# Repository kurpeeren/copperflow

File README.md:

# copperflow

**A PCB design program you and your AI agent use together.** The agent places, routes, checks and
exports the board through MCP, with or without a window open; you work in the same files in the
editor, and every change it makes is one step you can undo. Schematic, PCB, autorouting, DRC,
Gerbers, BOM and a 3D view, on your own computer.

[Website](https://copperflow.kurpeeren.com) ·
[Download the desktop app](https://github.com/kurpeeren/copperflow/releases/latest) ·
[Connect your agent](https://copperflow.kurpeeren.com/connect.html) ·
`npm install -g copperflow`

<table>
  <tr>
    <td width="50%"></td>
    <td width="50%"></td>
  </tr>
  <tr>
    <td>One agent session, an empty folder, no window open: 23 of 23 connections routed, 0 errors, 16 files for the factory.</td>
    <td>The board as made, drawn from the same Gerber layers the factory gets.</td>
  </tr>
</table>

Circuits are TSX files with elements such as `<board>`, `<resistor>` and `<trace>`, which
copperflow builds and draws with its own engine. You and your agent work on them together:

- the agent changes the circuit through an MCP server, and every change is one undo step;
- you lock the parts you have placed, and the agent cannot move or change them;
- you leave marks such as "route ground here", and the agent reads them;
- edits are written back as minimal text changes, so the rest of your code stays as you wrote it.

Everything runs locally. There is no chat inside copperflow: use the agent you already use,
for example Claude Code or Claude Desktop, through MCP.

> **Status: 0.5, early.** The core, the MCP server, the CLI, the editor, the desktop app, the parts
> library, placement, routing and the fabrication export work. Expect rough edges; see
> [docs/design.md](docs/design.md).

## Quick start

Requires Node.js 22 or newer.

```bash
npm install -g copperflow
```

To work on copperflow itself, install it from source instead:

```bash
git clone https://github.com/kurpeeren/copperflow.git
cd copperflow
npm install
npm run build
npm link
```

Try it on the example board (in the source tree):

```bash
copperflow summary --root examples/usb-c-ldo index.circuit.tsx
```

`copperflow check` (and the agent's `check_circuit`) runs copperflow's own rule checks and nothing else, so no other tool needs to be installed:

- the electrical rules check (ERC): pins left unconnected, outputs driven together, nets without a power source and so on;
- the placement design-rule check (DRC): overlapping courtyards, parts off the board, pads and holes too close to each other;
- problems in the code and the model, the same ones the Studio shows: a footprint it cannot make (`footprint`), a pin that does not exist (`unknown-pin`) or that several pins share (`ambiguous-pin`), an instance that overrides its library part (`library-override`) and so on.

Design rules live in `rules.yaml` at the project root: a fabrication profile (JLCPCB 2-layer by default), net classes and global nets. The `usb-c-ldo` example shows a small one, and `skills/copperflow/references/design-rules.md` explains the format and every check.

The CLI groups findings by code, with their positions; the agent's `check_circuit` lists them one per line, errors first. Any error fails the check (exit code 1). Copper checks (clearance between nets, track width, via drill and ring, board edge, keepouts, shorts) cover the tracks and vias in the layout file.

### Connect Claude Code

The copperflow plugin brings the MCP server and the copperflow skill in one install, for every project.
It starts the server through npx, so only Node.js is needed:

```bash
claude plugin marketplace add kurpeeren/copperflow
claude plugin install copperflow@copperflow
```

Inside a session, `/plugin marketplace add kurpeeren/copperflow` and `/plugin install copperflow@copperflow`
do the same. The server works on the folder the session starts in.

Without the plugin, from your circuit project:

```bash
claude mcp add copperflow -- copperflow mcp
```

The agent learns the workflow from the guide that comes with the server (the `guide` tool), so
nothing else is needed. To have the same text as a Claude Code skill, in `.claude/skills/copperflow`:

```bash
copperflow skill
```

`copperflow skill --global` installs it once for every project. Steps for other agents are at
<https://copperflow.kurpeeren.com/connect.html>.

### Connect Antigravity

Antigravity installs copperflow as a plugin, with the MCP server and both skills (`copperflow` and
`copperflow-plan`), for every project:

```bash
agy plugin install https://github.com/kurpeeren/copperflow
```

`agy plugin list` then shows copperflow with 2 skills and 1 MCP server. Start a new conversation in the
board's folder: the server starts through npx and works on that folder. For the server alone, put the
`copperflow` entry in `.agents/mcp_config.json` of the board's folder (or `~/.gemini/config/mcp_config.json`
for every project), in the same form as [`mcp_config.json`](mcp_config.json) at the root of this repository.

Any other MCP client can run `copperflow mcp` over stdio from the project folder
(or pass `--root <dir>`).

Without installing, the same server starts through npx: give `npx -y copperflow mcp` wherever a
client asks for the command. The first start takes about a quarter of a minute while npm fetches
the package.

An agent that can run commands can set copperflow up for itself: the steps are at
<https://copperflow.kurpeeren.com/llms.txt> as plain text. Most programs load their MCP servers
when a session starts, so the tools appear in the next session, not in the one that added them.

`copperflow connect claude-desktop` adds the server to Claude Desktop's config (it keeps every other
setting and leaves a backup of the original); `copperflow connect claude-code` prints the line for
Claude Code.

While a tool runs long (autoroute, autoplace, the exports, a 3D picture) the server sends MCP
progress notifications, so a client that shows them says "Routing: 3 of 8 connections". When the
Studio is open on the same project, every tool call also shows in a strip under its toolbar, and
`open_studio` brings that window to the front instead of opening another.

### Desktop app (Windows, macOS, Linux)

The [latest release](https://github.com/kurpeeren/copperflow/releases/latest) has the app with its own
runtime, so no Node.js or npm is needed: `copperflow-Setup.exe` for Windows (installs for the current
user), `copperflow-mac-arm64.dmg` or `copperflow-mac-x64.dmg` for macOS, and
`copperflow-linux-x86_64.AppImage` or `copperflow-linux-amd64.deb` for Linux. It opens to a start screen
(recent projects, open a folder, a new project) and then the Studio of that folder; File → Projects… goes
back, and the Files tab of Project Design shows the folder file by file, with a preview of its text and
pictures. The same program is the MCP server: the start screen's **Connect** writes it into
Claude Desktop, and **Copy the command** gives the line for Claude Code. An agent works headless; when
the window has its project open, the agent's changes and what it is doing appear there as it goes.

The apps are not signed with a developer certificate yet: Windows shows "Windows protected your PC" the
first time (More info, then Run anyway), and macOS asks once in System Settings, Privacy & Security (Open
Anyway). The release carries each file's SHA-256 beside it. Every version tag builds all of them
(`.github/workflows/desktop.yml`). To build one from source: `npm run build`, then in `desktop/`, `npm ci`
and `npm run dist` (Windows), `npm run dist:mac` or `npm run dist:linux`; the files are in `desktop/out/`.

### Open the visual editor

```bash
copperflow studio --root examples/usb-c-ldo
```

Then open the address it prints. The address carries a key for this session, so other web
pages and other programs on your computer cannot use the editor's API.

A connected agent opens it for you: ask it to open copperflow and it calls `open_studio`, which
starts the editor for the project if none runs and opens it in your browser. An editor started
that way stops by itself an hour after the last tab closes; `copperflow studio stop` stops it at once.

The schematic and the PCB are drawn from the design copperflow's engine builds, with
copperflow's own footprints and schematic symbols. The PCB shows the ratsnest, a straight line
for each connection still to be made, until it is routed by hand or by the router. A third tab,
3D, shows the board as it will be made with its parts on it (see [Pictures and 3D](#beyond-drawing)).

The window is laid out like a desktop EDA editor:

- The menu bar (File, Edit, View, Place, Design, Route, Layout, Tools, Export, Settings, Help) runs
  every command Studio has, and shows the ones still to come greyed out, with the stage or round
  that brings them. The build status sits at its right end; click it to see the checks.
- The toolbar under it holds the open document's tools: undo, zoom and fit, the schematic's Place
  tools (component, wire, net label, ground, power), rotate, Check DRC and the PCB's unit, and at
  its right end the snap grid, the PCB's layer switches and Keep these positions.
- The strip at the left edge opens Project Design or Common Library. Project Design has four
  tabs: Page (the project's circuit files, each with its Schematic and PCB), Net (every net; click
  one to highlight it in both views), Component (the parts) and Object (the connections).
- The strip at the right edge opens Properties: the selected part in Basic, Footprint, Position,
  Connections, Library and Notes sections, or, with nothing selected, the build, the notes for the
  agent and the bill of materials, which it exports with the datasheets.
- Document tabs above the canvas switch between the open file's Schematic and PCB.
- The strip at the bottom opens Library, Log (the history, with undo), DRC (the build's errors and
  warnings, which are ringed on the canvas; click one to go to it) and Find Results.

The mouse, in both views:

- Click a part to select it; Shift or Ctrl and click adds it or takes it out.
- Drag the background to draw a selection box: left to right takes the parts inside it, right to left
  the parts it touches; with Shift or Ctrl held it adds to the selection.
- Drag a part to move it, or a selected part to move the whole selection; parts snap to the grid
  (0.1, 0.5 or 1 mm on the PCB).
- Drag with the right (or middle) button to pan, and scroll to zoom.
- Double click a part to edit it in Properties.
- Place → Note box, then drag a box, leaves a note for the agent.

Press R to rotate and Delete to remove, lock parts, change values in Properties, draw wires in the
schematic as in KiCad (click a free pin, or press W over a pin, click the sheet for corners on the grid,
then click a pin, a net label or a wire; Esc cancels) and undo changes.
Drag a net label or a ground or power symbol in the schematic and its wire follows, written as `schematicRouteHints` on the trace (Esc cancels the drag).
The Place tools in the schematic toolbar (Net label, Ground flag, Power flag) put a label on a pin you click, written as a trace with one corner, and stay armed until Esc (while one is armed, dragging the background pans); Tab names a label before you click.
A double click on a net label renames its net everywhere; on a ground or power flag it asks first.
Design → Highlight net lights every net of the selected part.

Keys, ignored while you type in a field:

- `W` or `Alt+W` wires, `Alt+N` places a net label, `Space` or `R` rotates, `Delete` removes, `F` or `K` fits
- `H` highlights the net under the pointer, `Shift+H` clears it
- `Q` switches the PCB between mm and mil (display only), `Shift+F` searches the library
- On the PCB `U` rounds the corners of the selected tracks (Edit → Fillet tracks; with nothing selected, every
  track after a confirm) and `Shift+U` straightens them again; Design → Design rules sets the radius
- `[`, `]` and `\` hide and show the left, right and bottom panels; the bottom panel comes back on the tab it had
- `Ctrl+Z` undoes the last change, `Ctrl+O` goes to the circuit files under Project Design → Page
- `Ctrl+A` selects every part, `Ctrl+F` opens the find box (Enter lists what matches in Find Results)
- The arrow keys move the selection one grid step, `Shift` and an arrow ten steps
- With several parts selected, `Space` or `R` turns them together about the centre of the selection
- A right click without moving opens the context menu on a part, a net label or the empty canvas;
  `Shift+F10` or the menu key opens it on the selected part from the keyboard
- `Esc` clears the selection and puts the tools away
- In the menu bar the arrow keys move between the menus and their items, Enter or Space runs an
  item and Esc closes the menu; in every row of tabs the arrow keys move between the tabs.
  Help → Keys lists every key.

Every edit is written back into the circuit file and shows at once.
When the agent changes the file, the editor updates by itself.

The Library, in Common Library and in the bottom strip, places parts from your library or the
built-in parts (resistor, capacitor, LED and so on). Selecting a library part shows its maker,
MPN, supplier number, datasheet and checklist in Properties, and lets you mark it verified.
Library → New part… writes a part from its datasheet with a live footprint preview, and
Library → Import by LCSC number… fetches one from EasyEDA; both leave it not verified.

## How it works

**The editable subset.** copperflow only writes back to code it can read without running it:
a part needs a string-literal `name`, and a prop is editable when its value is a literal such
as `pcbX={4.5}` or `resistance="10k"`. Parts inside `.map()` or with spread props, and
expressions such as `pcbX={x + 2}`, are shown as read-only. Nothing else is restricted.

**Locks and marks.** They live next to the circuit in `board.circuit.annotations.json`, so
they stay out of the circuit code and git keeps them. Only you lock and unlock. The agent's tools
refuse to touch locked parts, and every summary reports a locked part that was changed some
other way.

**Parts library.** Chips and connectors live in `parts/<id>/part.yaml` in your project: pins
with names and electrical types, a footprint, MPN and supplier numbers. The footprint is either a
string such as `sot23_5`, from which copperflow makes the pads (the strings it knows are listed in
[editable-subset.md](skills/copperflow/references/editable-subset.md#footprint-strings), and
`copperflow packages [words]` browses the standard packages by name, with pads and size), or
`footprint.yaml`, a file next to `part.yaml` with every pad transcribed from the datasheet's
recommended land pattern; the example's USB-C connector has one. copperflow generates the part's
component from `part.yaml`. The agent creates parts from datasheets, or `copperflow parts import
C7950` fetches one by its LCSC number from EasyEDA (see [licences](docs/licences.md) for what the
source allows: personal, non-commercial use only; parts with letter-numbered pins such as BGAs are
refused); they stay *not verified*
until you check `verification.md`, which covers `footprint.yaml` too, and run
`copperflow parts verify`. An imported footprint keeps EasyEDA's orientation, which is JLCPCB's,
so pick-and-place needs no correction; place it at `pcbRotation -90` to match a generated footprint
of the same package.

**BOM and datasheet package.** `copperflow bom` groups parts by value, footprint and part
number; `copperflow package` writes the BOM, the local datasheets and every library part's
verification status into one folder. Both read the design copperflow builds from the circuit code,
so parts made in loops are counted, and supplier numbers come from the code and the library; there
is no `--build` option.

**History.** Every change made through copperflow is stored in `.copperflow/history/` with
who made it. `copperflow undo` reverts the newest change; the agent can undo only its own.
The agent sees what you undid and does not repeat it.

## Beyond drawing

**Checking a part against its datasheet.** Verify on a library part opens a screen in the Studio: the
footprint drawn with its dimensions, each pin as a row to tick, and the recorded datasheet beside them.
The part can be marked verified only when every item is ticked, and only a person can do it.

**What a change did.** `copperflow history <id>` (the agent's `recent_changes { id }`) says what one
change did: parts added, removed and moved, nets and copper; `--since <id>` covers everything after
it. `copperflow render <file> --change <id>` draws it on the board, and each row of the Studio's Log
has Show.

**Ready to order.** `copperflow bom` ends with whether the board is ready to order bare and ready for
assembly, and names the lines with no supplier part number. No price or stock is checked.

**Pin map for firmware.** `copperflow pins <file>` lists which net is on each pin of the chips and
connectors, as a table, CSV or a C header (`--format c`); `copperflow package` writes them too.

**Fabrication files.** `copperflow export <file>` writes the Gerbers, drills, pick-and-place file and
BOM for JLCPCB into `<name>-fab/` and a zip, with `<name>.step` for a mechanical CAD program and a
picture of each side of the board. A circuit with errors is refused.

**EasyEDA.** `copperflow easyeda <file>` (MCP `export` `as: "easyeda"`) writes the board as an EasyEDA Standard
PCB document, `<name>-easyeda.json`, which EasyEDA Standard opens as an editable PCB: outline, parts with their pads
and nets, tracks, vias, holes, texts and the pours as copper areas to rebuild there. `docs/easyeda-export.md` lists
what is written and what is left out.

**Pictures and 3D.** `copperflow render <file> --view board` draws the bare board as made: every
fabrication layer is drawn by itself, from the same data the Gerbers are written from, and they are
put together as mask, finish, print and holes, in the maker's usual colours (`--mask`, `--finish`,
`--silk`). `--view 3d` and the Studio's 3D tab lay that picture on the board and stand the parts on
it. `copperflow glb <file>` writes that same board and its parts as a GLB file, a 3D model a viewer, a
3D editor or a web page opens and turns; `copperflow step <file>` writes the STEP file alone. Both
write a board that is not finished too. `copperflow html <file>` (MCP `export` `as: "html"`) writes the whole design as
one web page to hand to someone: every schematic page, the PCB view, the board as made top and bottom,
3D from three angles and the BOM as a table, with the fabrication zip, the GLB, the STEP file and the
BOM as CSV inside it as downloads. It opens from disk with no network; a design with errors is written
too, without the fabrication files, and says why. The parts are simple shapes, not their real models, in the 3D
view, the GLB file and the STEP file; a part's height comes from its `height` in `part.yaml`, else a
typical figure for its package, else 1 mm, and the view says which.

**Fast lines.** Net classes in `rules.yaml` take an impedance, a differential pair with its gap and
skew, a longest length and length-matched groups; the checks report a pair that runs apart or differs
in length, and `copperflow impedance` gives widths and gaps for the board's stack. The figures are
estimates, and the router does not route pairs together or tune lengths yet. See
[design-rules.md](skills/copperflow/references/design-rules.md).

**Simulation.** `copperflow simulate` (the agent's `simulate`) finds the DC operating point from ideal
sources and simple part models: no time, no frequency, no temperature, no tolerance, and chips are not
modelled. A sheet's card can hold cases ("at 24 V in, the output is between 3.0 and 3.5 V") that it
runs; `copperflow spice` writes the same circuit as a SPICE netlist for another simulator.

**A board from KiCad.** `copperflow import kicad board.kicad_pcb` (the agent's `fit_board` with `drawing`, or
File, Import board in the Studio) makes a new circuit from a KiCad 6 or newer board: its outline,
parts, nets, tracks, vias and pours. The parts arrive as library parts, not verified.

## MCP tools

31 tools. Tools that do the same kind of thing to the same object are one tool with a parameter
(`view`, `as`, `redo`, `square`, …); [docs/design.md](docs/design.md) lists the old calls and their
new forms.

| Tool | What it does |
|------|--------------|
| `project_status` / `note_decision` | The project memory `PROJECT.md` (Intent, Blocks, Decisions, Open) with the circuit files, each circuit's counts and last changes; a dated decision (or with `open: true` one more open item), or with `sections` rewritten Intent, Blocks and Open, each write one change |
| `circuit_summary` | Compact by default (a line per part and net, locks, marks, lock violations); `detail: "full"` lists every prop and trace. `view: "board"`: the board in about 60 lines (size, one line per part, longest connections with both pads' places, overlaps, edge, pours); `view: "copper"`: per net the tracks, vias, length and unrouted connections, then copper violations by rule; `view: "bom"`: the bill of materials, with whether the board is ready to order |
| `edit_circuit` | Edits applied in order as one change (one history entry), stopping at the first refused edit and writing nothing: `set_props` (position, rotation, value, footprint; `schNameAt`, `schValueAt` and `pcbNameAt` take a point `{ x, y }`; `null` removes one of those), `place_part` (a library or built-in part, with its import), `remove_part` (with its traces), `disconnect`, `add_text` (a schematic note, or with `layer` board silkscreen), `add_pour` / `remove_pour` / `add_hole` / `remove_hole`, instances, pages, drawings |
| `add_trace` | Connects two ports or nets; with `nets` many pins of a circuit in one call, e.g. `{ "GND": ["R1.pin2", "C1.pin2"] }`, refusing unknown parts or pins and listing the pins it added |
| `check_circuit` | Runs copperflow's own ERC and placement DRC: counts, then up to 20 findings, one line each; `filter` narrows by severity, `copper`, part or net; copper clearance, width, via, board-edge and keepout violations are included |
| `new_circuit` | Writes a whole new circuit from a netlist in one call: parts (a built-in `kind` or a library `part`, `value`, `footprint`, `props` such as `pinCount` or a `pinLabels` object to name pins, no positions) and `nets` (`{ GND: ["R1.pin2", "U1.GND"] }`, no wire corners). Pins are checked first (a wrong one is refused with the part's real pin names); an existing file needs `replace: true`; one history entry, and undo removes the file. It then places the board (`autoplace`, a second entry; the board is fitted when no `board` size is given) unless `place: false` |
| `autoplace` | Places the parts nobody placed or locked (or only `parts`, or one `instance`) by their connections, as one change: answers "Placed 12 parts; wire length 184 mm (was 412); board 42 × 28 mm; 0 overlaps", then the parts it found no room for and its notes; `fit: true` fits the board too; `budgetSeconds` (20 s by default); `connectors: "ahead"` tries each connector beside the part it serves (route and compare before keeping it) |
| `fit_board` | Shrinks or grows a rectangular board to the parts' courtyards plus `margin` (2 mm by default), or sets a size, an outline or 4 copper layers, as one change; with `drawing` the outline, mounting holes and keepouts come from a DXF or SVG drawing in the project folder, and a `.kicad_pcb` file makes a new circuit from a KiCad board |
| `set_rules` | Changes `rules.yaml` (net classes, fabrication profile and minimums) as one change, and says what it means for the board |
| `autoroute` | Routes the unrouted connections (the whole board, some nets, some parts or one instance) and names each one it could not route with the reason |
| `route_track` | Draws one track of a net by hand from a pad, track or via of that net, as one change, refused when a point lands on another net's copper; with `at` places a via (net from the copper under it, size from the net class and the fabrication ring); the answer lists the copper violations it introduced |
| `remove_copper` | Removes tracks and vias by id (or one segment of a track by `{ id, segment }`), or with `nets` or `all: true` the router's copper, as one change |
| `fillet_tracks` | Rounds the square corners of tracks (by id, or every track) into short chords on an arc of the design rules' fillet radius, or with `square: true` puts rounded corners back, as one change; a corner too close to other copper, a pad, a keepout or the board edge, or with legs too short, stays as it was and is counted |
| `import_graphic` | Places a logo or mark from an SVG or DXF in the project on the board, as silkscreen or copper |
| `simulate` | The DC operating point of a circuit or a sheet: set nets to volts, close switches, energise relay coils; with a sheet and no values it runs the sheet's cases |
| `make_sheet` / `describe_sheet` | Moves parts into a sub-sheet with ports, and writes a sheet's card: what it does, its ports and its cases |
| `list_modules` / `use_module` / `save_module` | The shelf of modules and the libraries (`name` reads one), bring one into the project, save a described sheet |
| `export` | Writes files from the design: `as: "fabrication"` the fabrication files, the STEP model and the board's pictures (refused when the circuit has errors); `"step"` or `"glb"` one 3D model file, STEP for mechanical CAD or GLB for a 3D viewer (an unfinished board too); `"html"` one web page (schematic, board, 3D, BOM, with the fabrication and model files inside) to hand to a person, opening offline; `"package"` a folder with BOM, datasheets, part status and pin maps; `"easyeda"` the board as an EasyEDA Standard PCB document to open and edit there |
| `render` | A PNG of the board or of one schematic page, drawn by the Studio's own code; `view: "board"` is the bare board as made: mask, finish, print and holes drawn from the fabrication layers, either side, in the maker's usual colours; `view: "3d"` is that board with its parts as simple shapes, at an angle; `change` or `since` draws what a change did; `parts` zooms to some parts (needs the optional package `@napi-rs/canvas`) |
| `list_parts` | Shows the parts library; with `id` a part's data, its pads and checklist |
| `create_part` | Adds a part from a datasheet: pins, footprint string or footprint file, MPN, suppliers |
| `set_part_fields` | Sets a part's suppliers, MPN, manufacturer or description; with `datasheet` records the datasheet its pins came from |
| `import_part` | Fetches one part by its LCSC number from EasyEDA into `parts/<id>/`, unverified, for personal, non-commercial use only (see [licences](docs/licences.md)) |
| `recent_changes` | Recent changes by you and the agent, including undos; `id` says what one change did, `since` everything after it |
| `undo_change` | Undoes one of the agent's own changes; `redo: true` redoes one of its undos |
| `open_studio` | Starts the Studio for the project if none runs, opens it in your browser and answers with the address |
| `guide` | The copperflow skill's texts, for an agent that has no skills |

There is no unlock tool and no verify tool on purpose.

## CLI

```text
copperflow mcp                              start the MCP server on stdio
copperflow studio [--port n] [--idle-minutes n]
                                            open the visual editor at http://127.0.0.1:4777 (or a free port);
                                            with --idle-minutes it stops after n minutes with no tab open
copperflow studio stop                      stop the Studio of this folder
copperflow skill [--global]                 copy the copperflow skills into .claude/skills of this folder
                                            (or of your home folder), for agents that read skills
copperflow summary <file>                   print a circuit summary
copperflow check <file>                     list the errors and warnings of copperflow's own rule checks
copperflow lock <file> <part...>            lock parts so the agent cannot change them
copperflow unlock <file> <part...>          unlock parts
copperflow mark <file> <text> [--pcb x,y | --sch x,y]
                                            leave a note for the agent
copperflow unmark <file> <id>               remove a note
copperflow parts                            list the parts library
copperflow parts build                      regenerate part components after editing part.yaml
copperflow parts verify <id> --by <name> --against <datasheet, page>
                                            mark a part as checked against its datasheet
copperflow parts import <C-number> [--id <id>] [--replace]
                                            fetch a part by its LCSC number from EasyEDA into parts/,
                                            not verified (needs the internet; see docs/licences.md)
copperflow modules                          list the shelf of modules (COPPERFLOW_MODULES, default ~/.copperflow/modules)
copperflow modules verify <name> --by <name>
                                            mark a module (or <library>/<name>) as checked by you
copperflow modules remove <name>            take a module off the shelf
copperflow library                          list the libraries of modules: built in, git and folders
copperflow library add <name> <address or folder> [--ref <branch or tag>]
                                            add a library from git (https://, ssh:// or user@host:path)
                                            or a folder; its modules read NOT verified until you verify them
copperflow library update [name]            bring git libraries to the newest commit of their ref
copperflow library remove <name>            forget a library (a clone is deleted, a folder never)
copperflow packages [words...]              the standard packages with their footprint strings, pads and size
                                            (words narrow the list: soic, sot 5, sc70, crystal)
copperflow place <file> <part> <name> [key=value ...]
                                            add a library or built-in part to a circuit
copperflow bom <file> [--csv]               print the bill of materials
copperflow package <file> [--out dir]
                                            write BOM, datasheets, part status and pin maps to a folder
copperflow pins <file> [--part <name>] [--format md|csv|c]
                                            which net is on each pin of the library chips and connectors
copperflow export <file> [--out dir]        write the fabrication files for JLCPCB: Gerbers, drills,
                                            pick-and-place and BOM in <name>-fab/ and <name>-fab.zip
                                            beside the circuit (or in the project folder --out), with <name>.step
copperflow step <file> [--out file.step]   write the board and its parts (in colour, as the 3D view draws
                                            them) as a STEP file for CAD, <name>.step beside the circuit
copperflow easyeda <file> [--out file.json]
                                            write the board as an EasyEDA Standard PCB document to open and
                                            edit there, <name>-easyeda.json beside the circuit
copperflow glb <file> [--out file.glb] [--mask black] [--finish hasl] [--silk black]
                                            write the board as made and its parts (as simple shapes) as a GLB
                                            file a 3D viewer turns, <name>.glb beside the circuit
copperflow html <file> [--out file.html] [--mask black] [--finish hasl] [--silk black]
                                            write the design as one web page with its files inside,
                                            <name>.html beside the circuit
copperflow render <file> [--view pcb|schematic|board|3d] [--page <name>] [--parts U1,C3] [--width n] [--out file.png]
    board: the bare board as made [--side bottom] [--mask black] [--finish hasl] [--silk black] [--background #rrggbb]
    3d: the board as made with its parts as simple shapes [--angle top|bottom|front|iso] and the same look options
                [--change <id> | --since <id>]
                                            draw the board or a schematic page to a PNG, as the Studio shows it
                                            (<name>-pcb.png or <name>-schematic-<page>.png beside the circuit)
copperflow simulate <file> --set V12=12 --set CTRL=3.3 [--sheet <name>] [--closed SW1,J2] [--coil K1] [--all]
                                            the DC operating point from ideal sources and simple models: no time,
                                            no frequency, no temperature, no tolerance; chips are not modelled.
                                            With --sheet and no --set it runs the sheet's cases
copperflow spice <file> [--sheet <name>] [--set net=volts ...] [--out file.cir]
                                            write the same circuit as a SPICE3 netlist for another simulator
copperflow board <file> --dxf <path> [--layer <name>] [--units mm|inch] [--origin keep] [--replace]
                                            set the board's outline, holes and keepouts from a DXF drawing
copperflow import kicad <board.kicad_pcb> [--name <circuit name>] [--replace] [--origin keep]
                                            make a new circuit from a KiCad board: its outline, parts (as
                                            library parts, not verified), nets, tracks, vias and pours
copperflow impedance [--single 50] [--pair 90] [--gap 0.2] [--width 0.3]
                                            line widths and gaps for an impedance on the board's stack (rules.yaml);
                                            an estimate: the router does not route pairs together or tune lengths
copperflow history [--limit n]              list recent changes
copperflow history <id> | --since <id>      what one change did, or everything after it
copperflow undo [id]                        undo the newest change, or the given one
```

Every command accepts `--root <dir>` (default: the current directory).

## Libraries

A library is a folder of modules laid out as the shelf is: `modules/<Name>/` (or `<Name>/` at the top
when there is no `modules` folder), each holding `<Name>.sheet.tsx`, `parts/<id>/part.yaml` (and
`footprint.yaml`) and an optional `module.json`. copperflow comes with one, named `copperflow`; you
add your own:

```text
copperflow library add <name> <git address or folder> [--ref <branch or tag>]
copperflow library update [name]
copperflow library remove <name>
```

`copperflow library` lists them. The agent sees their modules as `<library>/<Name>` in
`list_modules` (with `name` for one) and `use_module`. A circuit file is code that runs when the board
builds, so a sheet from a library enters a project only when copperflow has proved it plain (part
imports, one function returning tags with literal values, nothing else), and its parts come as data,
their component files written by copperflow. A library module reads NOT verified until you run
`copperflow modules verify <library>/<Name> --by <name>`.

## Roadmap

- **0.2** (done) Visual editor in the browser: drag, rotate, lock, delete and reconnect wires, marks.
- **0.3** (done) Parts library (one folder per part) and datasheet-to-part import; BOM and datasheet package.
- **0.4** (done) Placement, routing, pours and the fabrication export; sheets, modules and libraries; part
  verification on screen, the change view, the order report, pin maps, STEP and the 3D view, fast-line rules,
  DC simulation, KiCad board import and the board drawn as made.
- **Next** Routing pairs together and tuning lengths, time and frequency in the simulator, real part models in 3D.

## Share your board

Share the one-page HTML from `export` `as: "html"` (or `copperflow html`) in
[GitHub Discussions, Show and tell](https://github.com/kurpeeren/copperflow/discussions/categories/show-and-tell). It shows
the schematic, the board, 3D and the BOM, and it runs no code from the project. Add the topic `copperflow-project` to a
repository that holds a copperflow project. To credit copperflow in its README:

```md

```

A copperflow project's `.circuit.tsx` files are code that runs when the project is opened, so open other people's
projects only when you trust them, and look at their HTML first.

## Contributing

See [CONTRIBUTING.md](CONTRIBUTING.md).

## License

Apache License 2.0. See [LICENSE](LICENSE) and [NOTICE](NOTICE). "copperflow" refers to this
project; the license does not grant rights to the name.

The visual editor bundles open-source packages (React, MIT). Their licences ship in
`dist/app/THIRD_PARTY_LICENSES.txt`.

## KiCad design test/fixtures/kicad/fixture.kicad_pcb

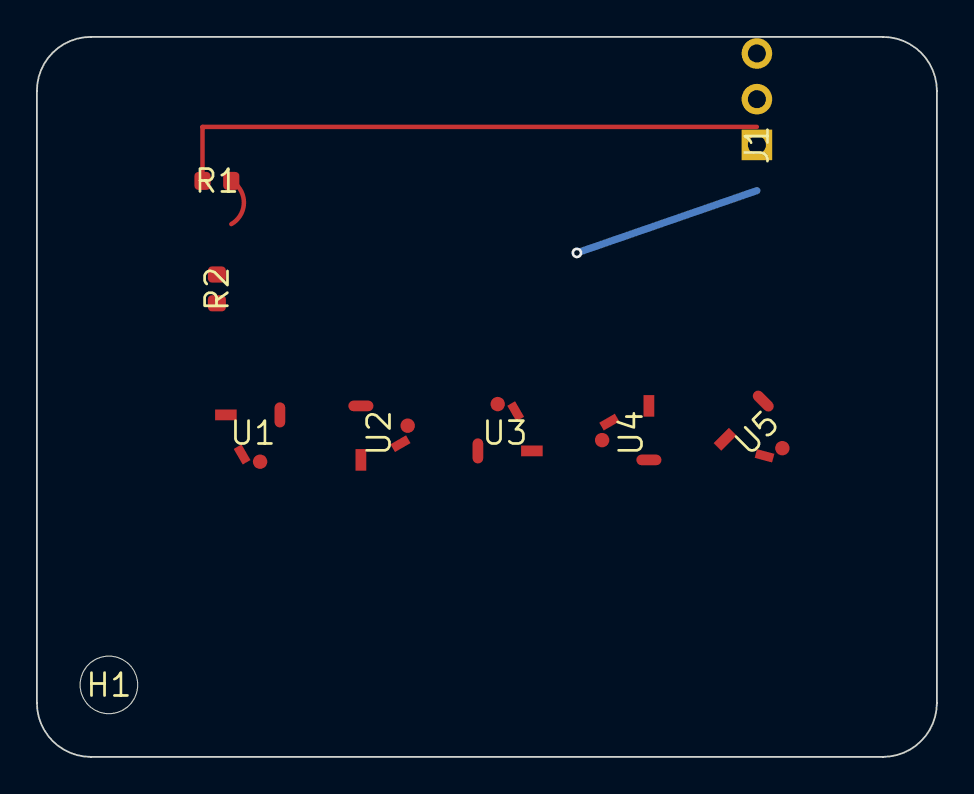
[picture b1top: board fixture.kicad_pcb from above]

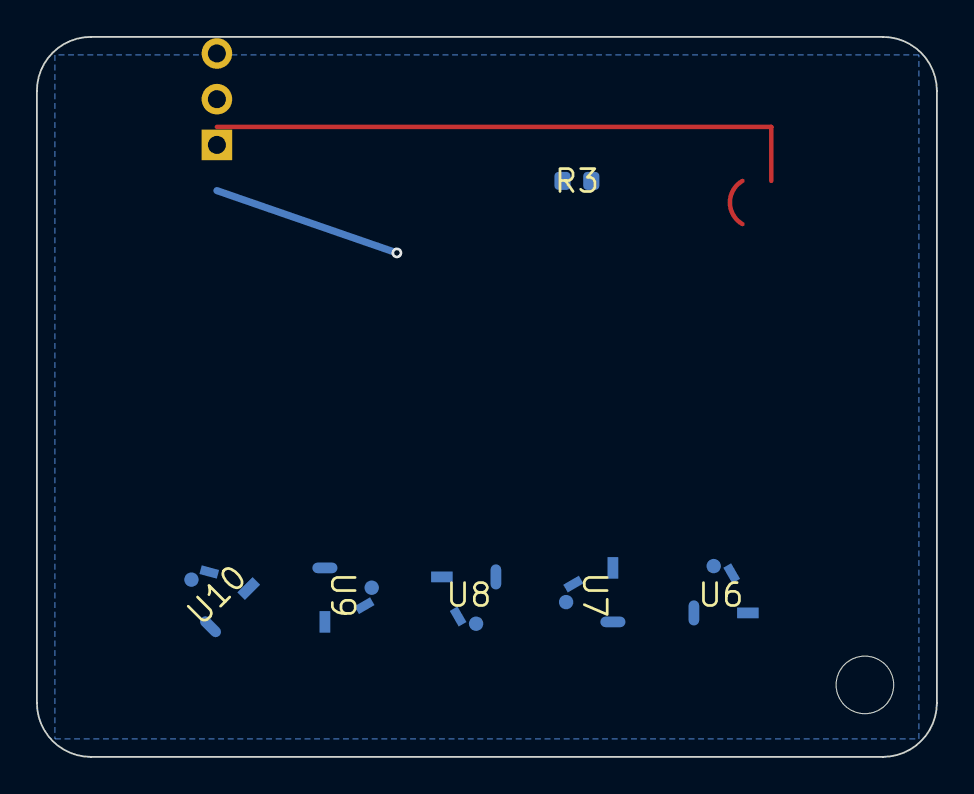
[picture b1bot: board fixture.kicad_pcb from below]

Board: 2 copper layers, 50.0 x 40.0 mm, 15 parts (6 on the bottom side), 4 nets.

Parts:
H1: MH; MH_fixture
J1: CONN3; CONN3_fixture
R1, R2: 10k; R_fixture_1608
R3: 1k; R_fixture_1608
U1, U2, U3, U4, U5, U6, U7, U8, U9, U10: ODD3; ODD3_fixture

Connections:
GND: J1.2, R2.2, U1.3 (GND), U2.3 (GND), U3.3 (GND), U4.3 (GND), U5.3 (GND), U6.3 (GND), U7.3 (GND), U8.3 (GND), U9.3 (GND), U10.3 (GND)
unnamed: R1.2, R2.1, U1.1 (IN)
OUT_A: R3.2, U1.2 (OUT)
VCC: J1.1, R1.1, R3.1

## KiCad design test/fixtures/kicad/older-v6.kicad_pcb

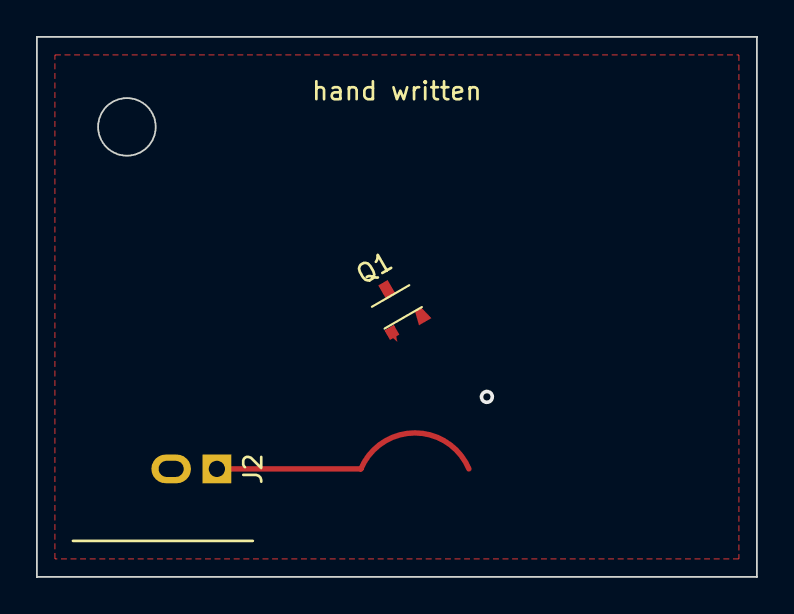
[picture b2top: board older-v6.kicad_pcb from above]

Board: 2 copper layers, 40.0 x 30.0 mm, 3 parts (1 on the bottom side), 3 nets.

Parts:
J2: HDR2; Header_like
Q1: BSS_like; SOT_like
R5: 4k7; R_like

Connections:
+5V: J2.1, R5.2
GND: J2.2, Q1.1
unnamed: Q1.3, R5.1
